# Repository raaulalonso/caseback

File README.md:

# Caseback software

Caseback is a biometric sensor worn under a wristwatch. This repository contains
the Bluetooth protocol, firmware and iPhone software.

| Directory | Contents |
| --- | --- |
| [caseback-protocol](caseback-protocol/) | BLE framing and messages, the Python implementation, generated test vectors |
| [firmware](firmware/) | Zephyr application for nRF52840 and an Arduino sensor recorder |
| [apps/ios](apps/ios/) | SwiftUI app, widgets, Swift protocol package and tests |

Run the protocol tests with `swift test --package-path apps/ios/CasebackProtocol`.
For Python 3.12 or later, create a virtual environment, install
`caseback-protocol/python[dev]` and run `python -m pytest caseback-protocol/python/tests`.
Build instructions are included for the [firmware](firmware/caseback-fw/README.md)
and [iOS app](apps/ios/README.md).

Caseback-owned software is available under [Apache-2.0](LICENSE). Bundled IBM Plex
fonts use the SIL Open Font License. See [NOTICE](NOTICE) for attribution.

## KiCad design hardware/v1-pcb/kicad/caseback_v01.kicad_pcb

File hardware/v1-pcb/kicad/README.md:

# V0.1 board in KiCad

`caseback_v01.kicad_pcb` is the board, `caseback_v01.kicad_sch` its schematic, `fab/` the files for JLCPCB. The stack
of the disc is in `../board_v01.py`.

The board is made by scripts, so a change to a part or a net starts in `netlist_v01.py` and not in KiCad.

## Tools

- KiCad 10 (its `kicad-cli` and the Python that comes with it, which has `pcbnew`). The scripts look for it in
  `~/Applications/KiCad/KiCad.app`; `KICAD_CLI` overrides the path of `kicad-cli`.

### Setting the tools up again

Versions used for the board in this folder (28 October 2026):

| Tool | Version | Where it came from |
|------|---------|--------------------|
| KiCad | 10.0.7 | the macOS app, copied to `~/Applications/KiCad/` |
| KiCad MCP server | 2.8.3 (mixelpixx/KiCAD-MCP-Server, `stable`, MIT) | Cloned to `Caseback-pcb-archive/tools/kicad-mcp-server`, built with `npm ci --ignore-scripts`, with its Python requirements in a venv made from KiCad's own Python (`KICAD_PYTHON`, and `KICAD_CLI` for the DRC). Registered in Claude Code with `claude mcp add kicad`. It opens and checks the board through `pcbnew` and `kicad-cli`; the layout is still made by the scripts here |
| PyMuPDF | any recent | `pip install pymupdf`, for the PNG renders of the SVG files |
| easyeda2kicad | 1.0.1 | `pip install easyeda2kicad`, which made `lib/` from the LCSC part numbers |

`tools/pcbcheck.sh DIR [FILE]` runs the DRC and renders the two faces. The older routing runs, the tools used for them and
the second-opinion checker (KiCadRoutingTools 0.23.7, github.com/drandyhaas/KiCadRoutingTools: clearance, connectivity,
pads, odd copper) are kept outside the repository in a folder called `Caseback-pcb-archive`.

## Order

Run each script with KiCad's Python (`python3 -I script.py ...`).

1. `build_v01_pcb.py`: outline, parts, vias in pads, rules, ground plane, antenna keep-out. It made the first placement; the
   board in this folder is the source of the placement now, and the builder is not run again for a routing change.
2. `route_v01.py IN OUT`: takes off every wire and via except the vias in pads and the two links of the module, and draws
   them again (see below). It takes about 40 s.
3. `finalize_v01.py IN OUT DRC.json`: removes vias that join one layer only (the DRC report names them) and refills the zones.
4. `polish_v01.py`: the antenna link, the keep-out, the SFH 7072 pads, via filling marks, zero-length wires.
5. `build_v01_sch.py` then `compare_netlists_v01.py`: schematic from the netlist and the check against the board.
6. `audit_v01.py`: wire length and vias per net.
7. `export_jlcpcb_v01.py`: Gerber and drill zip, BOM, placement file.

### The routing

`manhattan.py` is a router that draws at 0, 45 and 90 degrees on a 0.05 mm grid and nothing else, with one width per net
class: 0.10 mm for signals, 0.15 mm for the supply and the LED nets, clearance 0.10 mm (0.15 mm at the photodiode inputs),
vias 0.30 / 0.15 mm. It searches F.Cu, In2.Cu and B.Cu; In1.Cu is the ground plane. The prices in `route_v01.py` make F.Cu
run along x and In2.Cu along y, keep turns to 45 degrees, and keep the skin side to short stubs. `route_v01.py` is the
driver that knows the board:

- the four lanes of the optics (the two photodiode inputs and the returns of two LEDs) are drawn by hand in the script as
  straight runs on F.Cu with a via in each end pad; the router only keeps away from them;
- ground pads get a short stub to a via, or a via of their own: the plane does the rest;
- then every other net, in the order of `ORDER`. A net it cannot join goes first in the next try, up to six tries;
- a via is either inside a pad or clear of it, never across its edge, and costs more inside a pad;
- vias that join one layer and wires that end in nothing are dropped at the end.

The module's signals go to the pads listed in `netlist_v01.U5_PADS` (the script sets them before routing).

It is a router written for this board with some lanes drawn by hand, not a fully hand-drawn board. The result was checked by
looking at each layer, and by the KiCad DRC, the KiCad MCP server and the second-opinion checker.

Edits to the reference board that are not a new route:

- `charge_pads_to_skin_v01.py IN.kicad_pcb OUT.kicad_pcb` moves the two charge pads from F.Cu to B.Cu (D52). It was run on
  the board of the 32 mm disc; the builder now draws the pads on B.Cu from the start, so the 25 mm board did not need it. After any edit of this kind run
  `tools/pcbcheck.sh` (it refills the zones and saves the board), then steps 5 to 7.
- `tools/dump_footprints.py BOARD OUT.json` writes the position, side and pads of every part. `placement_v01.json` is its
  output for the reference board: the 3D model of the disc and `board_v01.py` read it, so run it again after the board
  changes.
- `tools/dump_copper.py BOARD OUT.json` writes the pads, wires, vias and zones of the copper in the disc frame. 
- `tools/densify_outline.py` writes a copy of the board with the round outline made of short segments, which is the form
  KiCad's glTF export needs to give a round board.

## Data from other sources

`lib/lcsc.pretty` and `lib/lcsc_symbols` are footprints and symbols from EasyEDA/LCSC for the parts in the BOM. Their
licence is not stated; treat them as the parts' manufacturer data and check them against the datasheets before ordering.

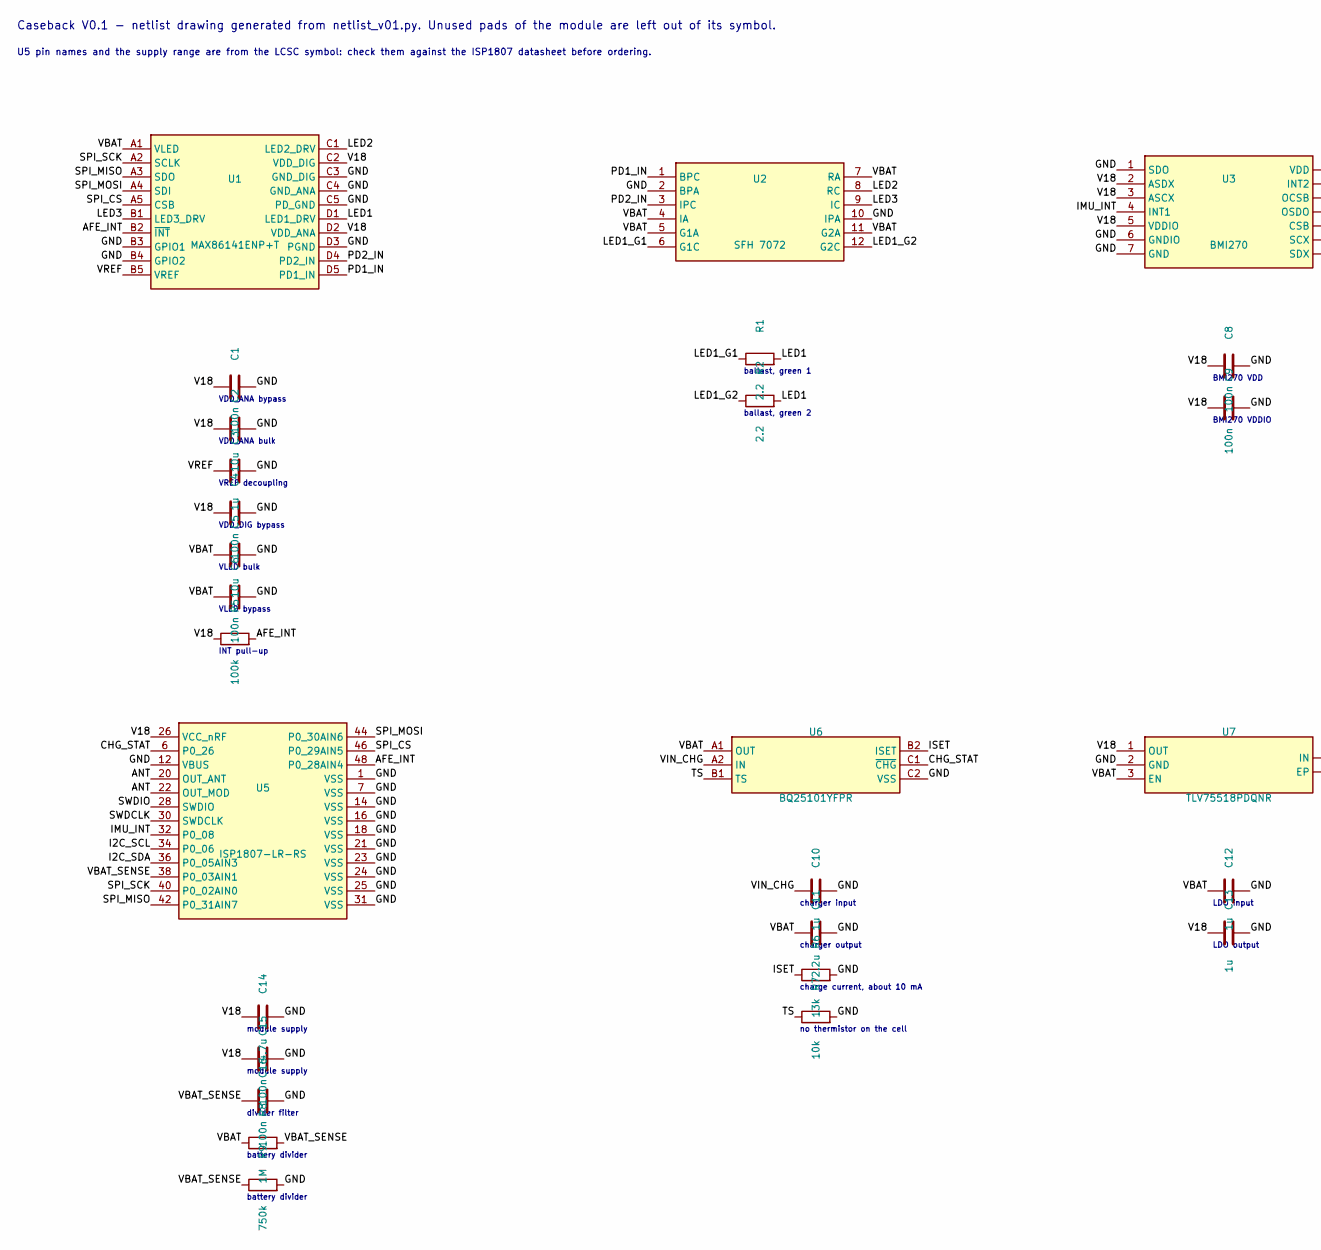
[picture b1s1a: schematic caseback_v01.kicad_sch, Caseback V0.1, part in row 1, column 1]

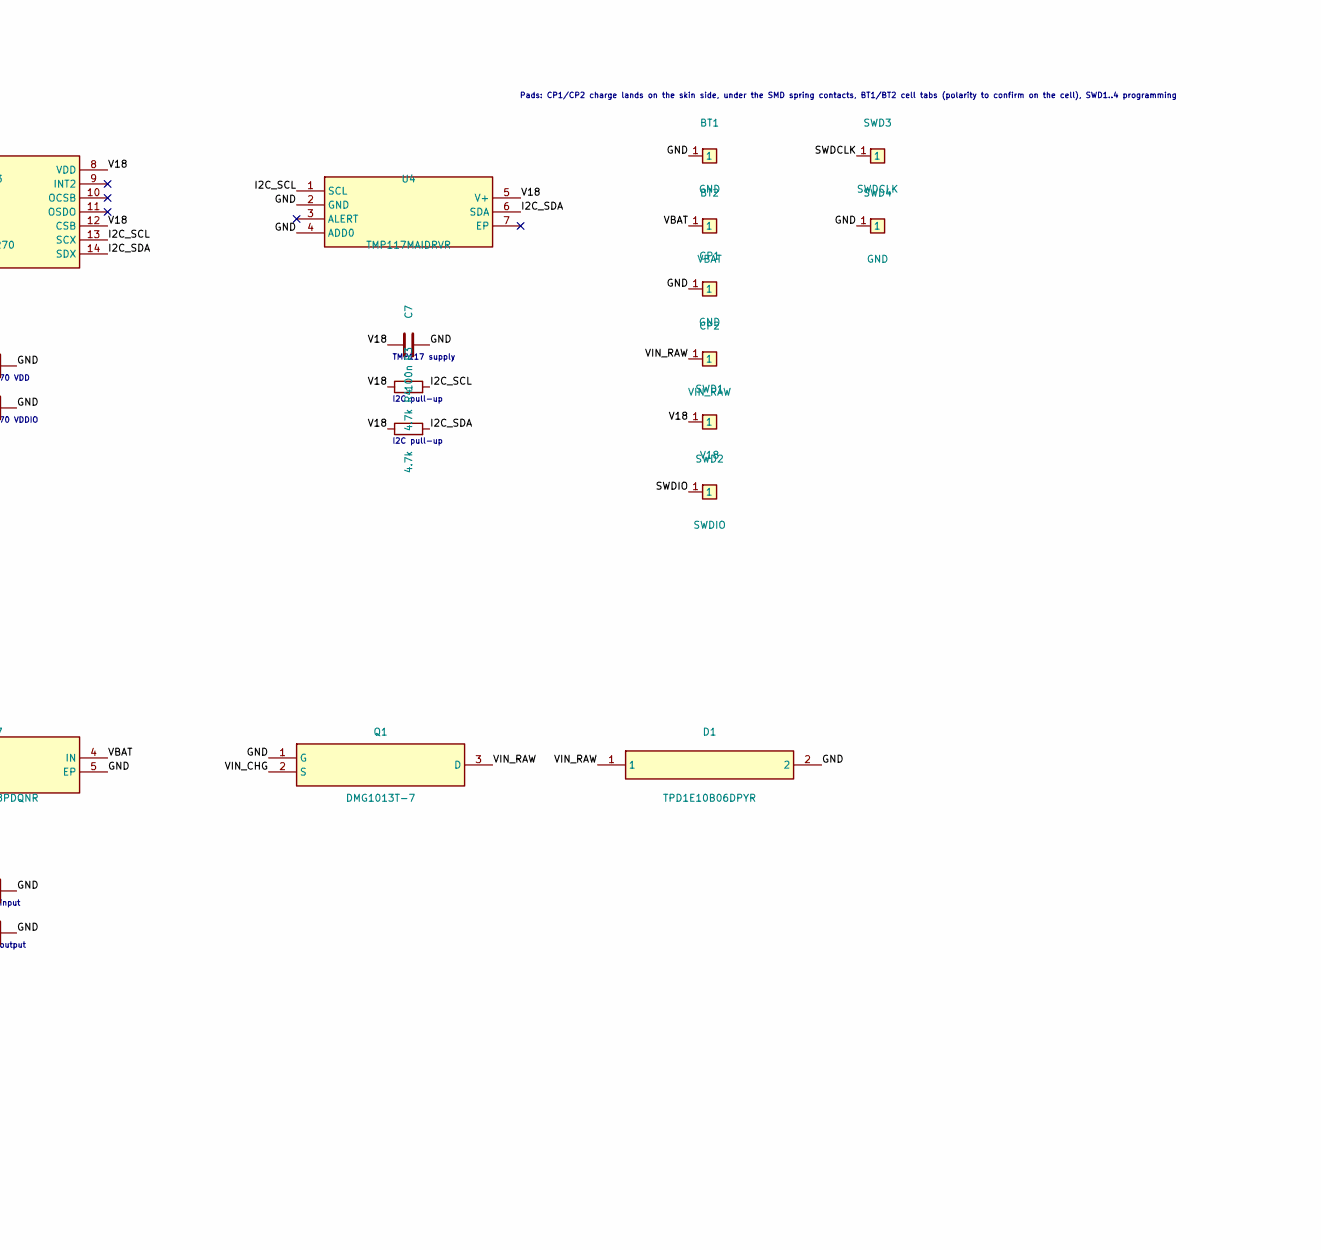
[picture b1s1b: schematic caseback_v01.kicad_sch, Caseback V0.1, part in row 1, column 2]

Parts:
BT1: GND; pad
BT2: VBAT; pad
C1, C4, C6, C7, C8, C9, C15, C16: 100n; 0402; LCSC C1525
C2, C5: 10u; 0402; LCSC C15525
C3, C10, C12, C13: 1u; 0402; LCSC C52923
C11: 2.2u; 0402; LCSC C12530
C14: 4.7u; 0402; LCSC C23733
CP1: GND; pad
CP2: VIN_RAW; pad
D1: TPD1E10B06DPYR; X1SON-2_L1.0-W0.6-P0.65-BI-1; LCSC C48260
Q1: DMG1013T-7; SC-75-3_L1.6-W0.8-P1.00-LS1.6-BR; LCSC C96676
R1, R2: 2.2; 0402; LCSC C25101
R3, R4: 4.7k; 0402; LCSC C25900
R5: 100k; 0402; LCSC C25741
R6: 13k; 0402; LCSC C25754
R7: 10k; 0402; LCSC C25744
R8: 1M; 0402; LCSC C26083
R9: 750k; 0402; LCSC C122545
SWD1: V18; pad
SWD2: SWDIO; pad
SWD3: SWDCLK; pad
SWD4: GND; pad
U1: MAX86141ENP+T; BGA-20_L2.0-W1.8-R4-C5-P0.40-TL; LCSC C5328762
U2: SFH 7072; DFN-12_L7.5-W3.9-P1.20-BL; LCSC C2655172
U3: BMI270; LGA-14_L3.0-W2.5-P0.50-BR; LCSC C2836813
U4: TMP117MAIDRVR; WSON-6_L2.0-W2.0-P0.65-BL-EP; LCSC C2803242
U5: ISP1807-LR-RS; BULETM-SMD_ISP1807; LCSC C5264268
U6: BQ25101YFPR; DSBGA-6_L0.9-W1.6-R2-C3-P0.40-BL; LCSC C478468
U7: TLV75518PDQNR; X2SON-4_L1.0-W1.0-P0.65-TL-EP; LCSC C2867154

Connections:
AFE_INT: R5.2, U1.B2 (~INT), U5.48 (P0_28AIN4)
ANT: U5.20 (OUT_ANT), U5.22 (OUT_MOD)
CHG_STAT: U5.6 (P0_26), U6.C1 (~CHG)
GND: BT1.1, C1.2, C2.2, C3.2, C4.2, C5.2, C6.2, C7.2, C8.2, C9.2, C10.2, C11.2, C12.2, C13.2, C14.2, C15.2, C16.2, CP1.1, D1.2, Q1.1 (G), R6.2, R7.2, R9.2, SWD4.1, U1.B3 (GPIO1), U1.B4 (GPIO2), U1.C3 (GND_DIG), U1.C4 (GND_ANA), U1.C5 (PD_GND), U1.D3 (PGND), U2.2 (BPA), U2.10 (IPA), U3.1 (SDO), U3.6 (GNDIO), U3.7 (GND), U4.2 (GND), U4.4 (ADD0), U5.1 (VSS), U5.7 (VSS), U5.12 (VBUS), U5.14 (VSS), U5.16 (VSS), U5.18 (VSS), U5.21 (VSS), U5.23 (VSS), U5.24 (VSS), U5.25 (VSS), U5.31 (VSS), U6.C2 (VSS), U7.2 (GND), U7.5 (EP)
I2C_SCL: R3.2, U3.13 (SCX), U4.1 (SCL), U5.34 (P0_06)
I2C_SDA: R4.2, U3.14 (SDX), U4.6 (SDA), U5.36 (P0_05AIN3)
IMU_INT: U3.4 (INT1), U5.32 (P0_08)
ISET: R6.1, U6.B2 (ISET)
LED1: R1.2, R2.2, U1.D1 (LED1_DRV)
LED1_G1: R1.1, U2.6 (G1C)
LED1_G2: R2.1, U2.12 (G2C)
LED2: U1.C1 (LED2_DRV), U2.8 (RC)
LED3: U1.B1 (LED3_DRV), U2.9 (IC)
PD1_IN: U1.D5 (PD1_IN), U2.1 (BPC)
PD2_IN: U1.D4 (PD2_IN), U2.3 (IPC)
SPI_CS: U1.A5 (CSB), U5.46 (P0_29AIN5)
SPI_MISO: U1.A3 (SDO), U5.42 (P0_31AIN7)
SPI_MOSI: U1.A4 (SDI), U5.44 (P0_30AIN6)
SPI_SCK: U1.A2 (SCLK), U5.40 (P0_02AIN0)
SWDCLK: SWD3.1, U5.30 (SWDCLK)
SWDIO: SWD2.1, U5.28 (SWDIO)
TS: R7.1, U6.B1 (TS)
V18: C1.1, C2.1, C4.1, C7.1, C8.1, C9.1, C13.1, C14.1, C15.1, R3.1, R4.1, R5.1, SWD1.1, U1.C2 (VDD_DIG), U1.D2 (VDD_ANA), U3.2 (ASDX), U3.3 (ASCX), U3.5 (VDDIO), U3.8 (VDD), U3.12 (CSB), U4.5 (V+), U5.26 (VCC_nRF), U7.1 (OUT)
VBAT: BT2.1, C5.1, C6.1, C11.1, C12.1, R8.1, U1.A1 (VLED), U2.4 (IA), U2.5 (G1A), U2.7 (RA), U2.11 (G2A), U6.A1 (OUT), U7.3 (EN), U7.4 (IN)
VBAT_SENSE: C16.1, R8.2, R9.1, U5.38 (P0_03AIN1)
VIN_CHG: C10.1, Q1.2 (S), U6.A2 (IN)
VIN_RAW: CP2.1, D1.1, Q1.3 (D)
VREF: C3.1, U1.B5 (VREF)

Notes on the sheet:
VDD_ANA bypass
VDD_ANA bulk
VREF decoupling
VDD_DIG bypass
VLED bulk
VLED bypass
INT pull-up
ballast, green 1
ballast, green 2
BMI270 VDD
BMI270 VDDIO
TMP117 supply
I2C pull-up
module supply
divider filter
battery divider
charger input
charger output
charge current, about 10 mA
no thermistor on the cell
LDO input
LDO output
Pads: CP1/CP2 charge lands on the skin side, under the SMD spring contacts, BT1/BT2 cell tabs (polarity to confirm on the cell), SWD1..4 programming
Caseback V0.1 - netlist drawing generated from netlist_v01.py. Unused pads of the module are left out of its symbol.
U5 pin names and the supply range are from the LCSC symbol: check them against the ISP1807 datasheet before ordering.

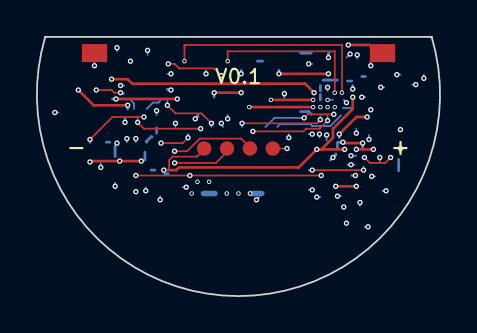
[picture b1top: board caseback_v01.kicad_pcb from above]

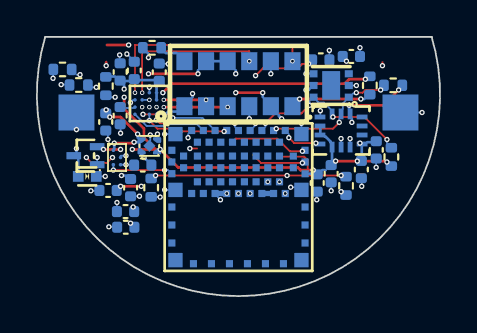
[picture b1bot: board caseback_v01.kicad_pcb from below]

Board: 4 copper layers, 22.4 x 14.4 mm, 42 parts (36 on the bottom side), 28 nets.

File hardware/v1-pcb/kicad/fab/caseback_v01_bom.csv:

Comment,Designator,Footprint,LCSC Part #
100n F,"C1,C4,C6,C7,C8,C9,C15,C16",0402,C1525
1u F,"C3,C10,C12,C13",0402,C52923
2.2u F,C11,0402,C12530
4.7u F,C14,0402,C23733
10u F,"C2,C5",0402,C15525
TPD1E10B06DPYR,D1,X1SON-2,C48260
DMG1013T-7,Q1,SC-75-3,C96676
2.2 ohm,"R1,R2",0402,C25101
4.7k ohm,"R3,R4",0402,C25900
100k ohm,R5,0402,C25741
13k ohm,R6,0402,C25754
10k ohm,R7,0402,C25744
1M ohm,R8,0402,C26083
750k ohm,R9,0402,C122545
MAX86141ENP+T,U1,BGA-20,C5328762
SFH 7072,U2,DFN-12,C2655172
BMI270,U3,LGA-14,C2836813
TMP117MAIDRVR,U4,WSON-6,C2803242
ISP1807-LR-RS,U5,BULETM-SMD,C5264268
BQ25101YFPR,U6,DSBGA-6,C478468
TLV75518PDQNR,U7,X2SON-4,C2867154
